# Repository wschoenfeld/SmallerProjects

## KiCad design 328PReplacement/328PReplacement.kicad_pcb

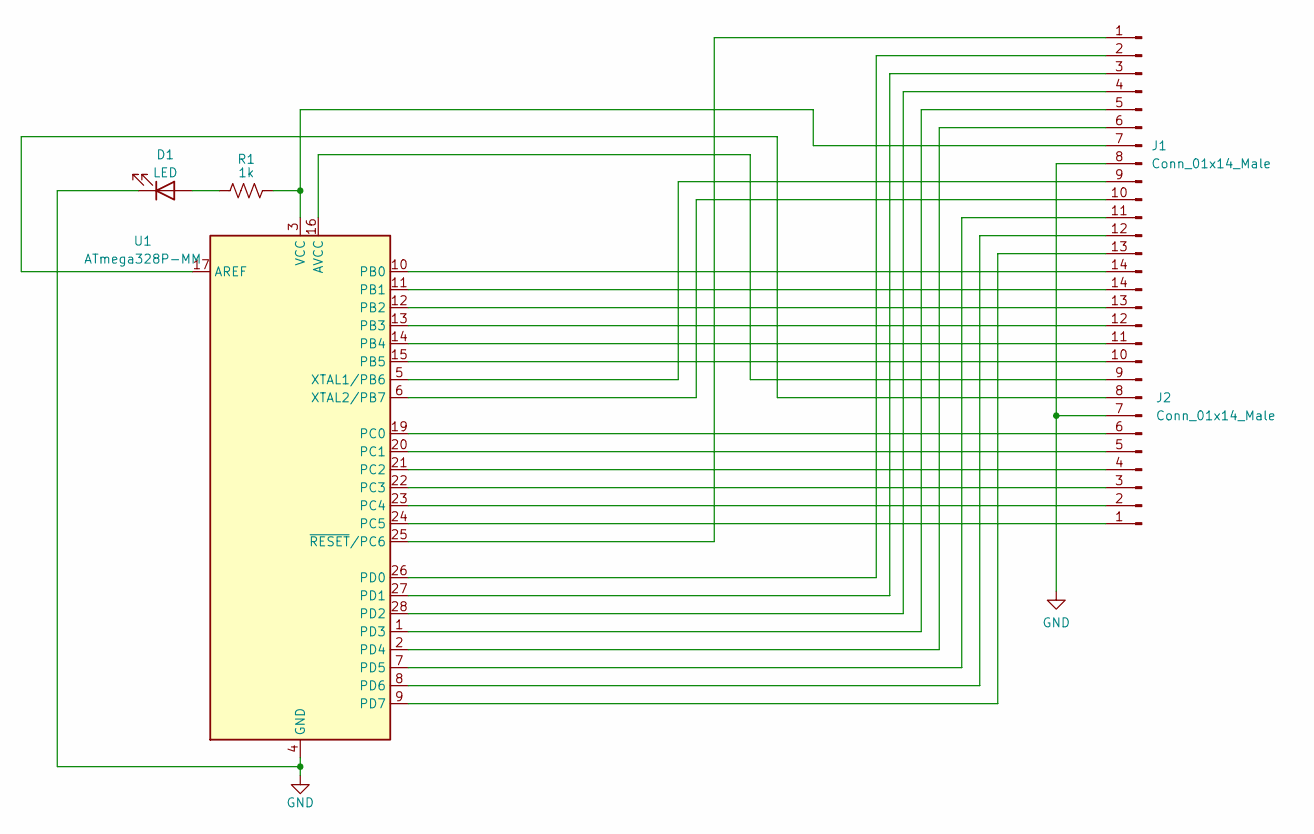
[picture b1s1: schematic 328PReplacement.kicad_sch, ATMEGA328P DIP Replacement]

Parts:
D1: LED; LED_0402_1005Metric
J1, J2: Conn_01x14_Male; PinHeader_1x14_P2.54mm_Vertical
R1: 1k; R_0402_1005Metric
U1: ATmega328P-MM; QFN-28-1EP_4x4mm_P0.45mm_EP2.4x2.4mm

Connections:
GND: D1.1 (K), J1.8, J2.7, U1.4 (GND), U1.18 (GND), U1.29 (GND)
unnamed: D1.2 (A), R1.1
unnamed: J1.1, U1.25 (~RESET/PC6)
unnamed: J1.2, U1.26 (PD0)
unnamed: J1.3, U1.27 (PD1)
unnamed: J1.4, U1.28 (PD2)
unnamed: J1.5, U1.1 (PD3)
unnamed: J1.6, U1.2 (PD4)
unnamed: J1.7, R1.2, U1.3 (VCC)
unnamed: J1.9, U1.5 (XTAL1/PB6)
unnamed: J1.10, U1.6 (XTAL2/PB7)
unnamed: J1.11, U1.7 (PD5)
unnamed: J1.12, U1.8 (PD6)
unnamed: J1.13, U1.9 (PD7)
unnamed: J1.14, U1.10 (PB0)
unnamed: J2.1, U1.24 (PC5)
unnamed: J2.2, U1.23 (PC4)
unnamed: J2.3, U1.22 (PC3)
unnamed: J2.4, U1.21 (PC2)
unnamed: J2.5, U1.20 (PC1)
unnamed: J2.6, U1.19 (PC0)
unnamed: J2.8, U1.17 (AREF)
unnamed: J2.9, U1.16 (AVCC)
unnamed: J2.10, U1.15 (PB5)
unnamed: J2.11, U1.14 (PB4)
unnamed: J2.12, U1.13 (PB3)
unnamed: J2.13, U1.12 (PB2)
unnamed: J2.14, U1.11 (PB1)

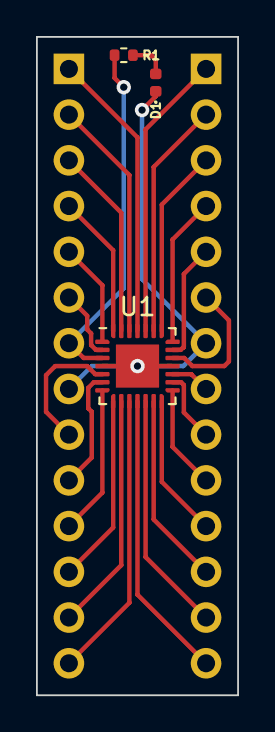
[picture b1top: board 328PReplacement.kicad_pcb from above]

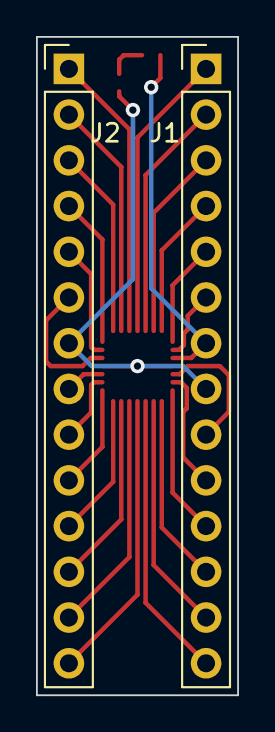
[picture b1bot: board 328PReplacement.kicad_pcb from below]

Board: 2 copper layers, 11.2 x 36.6 mm, 5 parts (2 on the bottom side), 28 nets.

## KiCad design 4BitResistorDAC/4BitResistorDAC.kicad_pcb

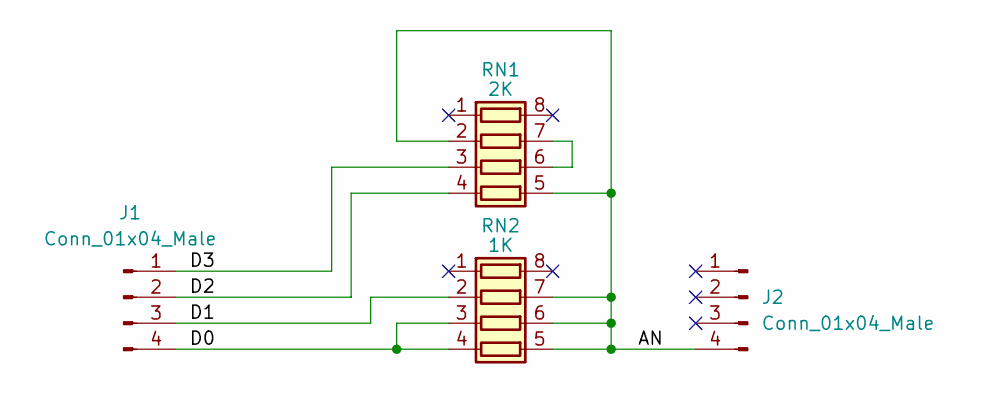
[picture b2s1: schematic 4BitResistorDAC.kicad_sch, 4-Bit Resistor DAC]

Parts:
J1, J2: Conn_01x04_Male; PinHeader_1x04_P2.54mm_Vertical
RN1: 2K; R_Array_Convex_4x0603
RN2: 1K; R_Array_Convex_4x0603

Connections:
/AN: J2.4, RN1.2 (R2.1), RN1.5 (R4.2), RN2.5 (R4.2), RN2.6 (R3.2), RN2.7 (R2.2)
/D0: J1.4, RN2.3 (R3.1), RN2.4 (R4.1)
/D1: J1.3, RN2.2 (R2.1)
/D2: J1.2, RN1.4 (R4.1)
/D3: J1.1, RN1.3 (R3.1)
unnamed: RN1.6 (R3.2), RN1.7 (R2.2)

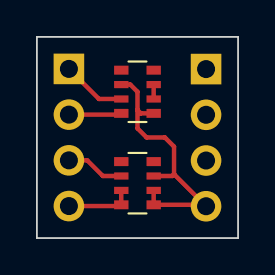
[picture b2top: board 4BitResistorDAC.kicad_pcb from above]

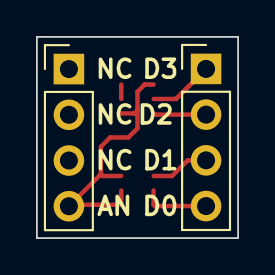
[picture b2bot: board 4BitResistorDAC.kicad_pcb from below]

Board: 2 copper layers, 11.2 x 11.2 mm, 4 parts (2 on the bottom side), 6 nets.

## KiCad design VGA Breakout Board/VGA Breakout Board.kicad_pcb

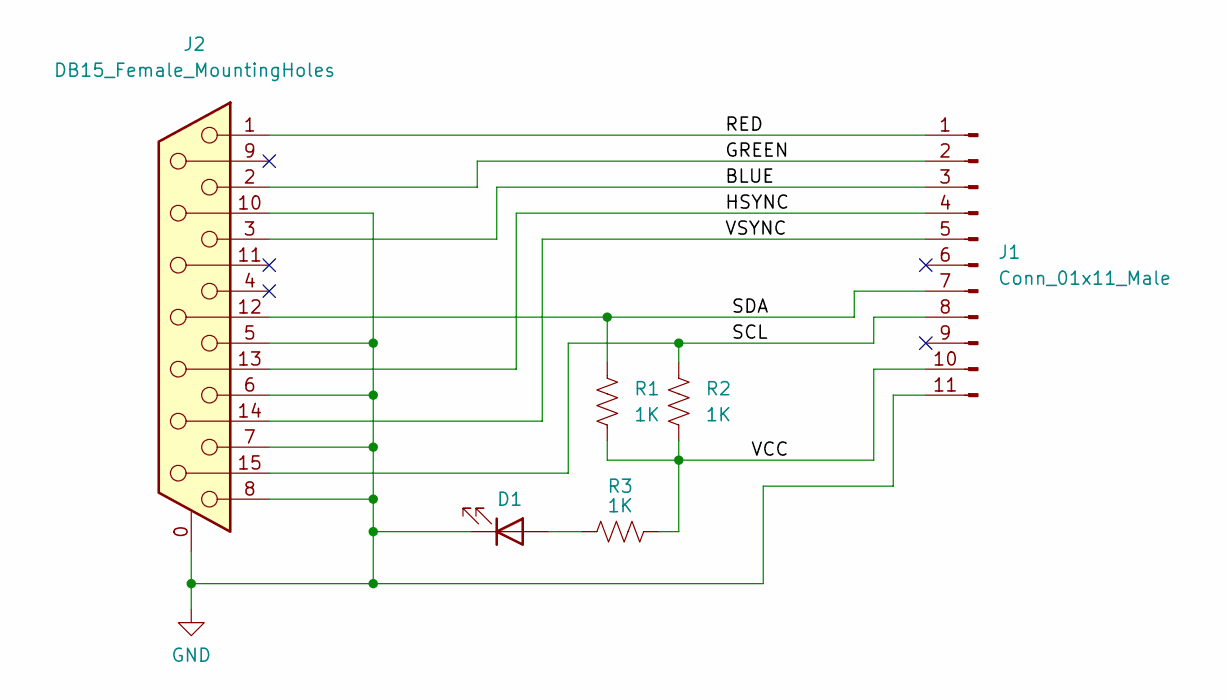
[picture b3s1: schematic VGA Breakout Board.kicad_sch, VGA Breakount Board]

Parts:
D1: LED; LED_0805_2012Metric_Pad1.15x1.40mm_HandSolder
J1: Conn_01x11_Male; PinHeader_1x11_P2.54mm_Vertical
J2: DB15_Female_MountingHoles; DSUB-15-HD_Female_Horizontal_P2.29x1.98mm_EdgePinOffset3.03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
R1, R2, R3: 1K; R_0805_2012Metric_Pad1.20x1.40mm_HandSolder

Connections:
/BLUE: J1.3, J2.3
/GREEN: J1.2, J2.2
/HSYNC: J1.4, J2.13
/RED: J1.1, J2.1
/SCL: J1.8, J2.15, R2.1
/SDA: J1.7, J2.12, R1.1
/VCC: J1.10, R1.2, R2.2, R3.2
/VSYNC: J1.5, J2.14
GND: D1.1 (K), J1.11, J2.0 (PAD), J2.5, J2.6, J2.7, J2.8, J2.10
unnamed: D1.2 (A), R3.1

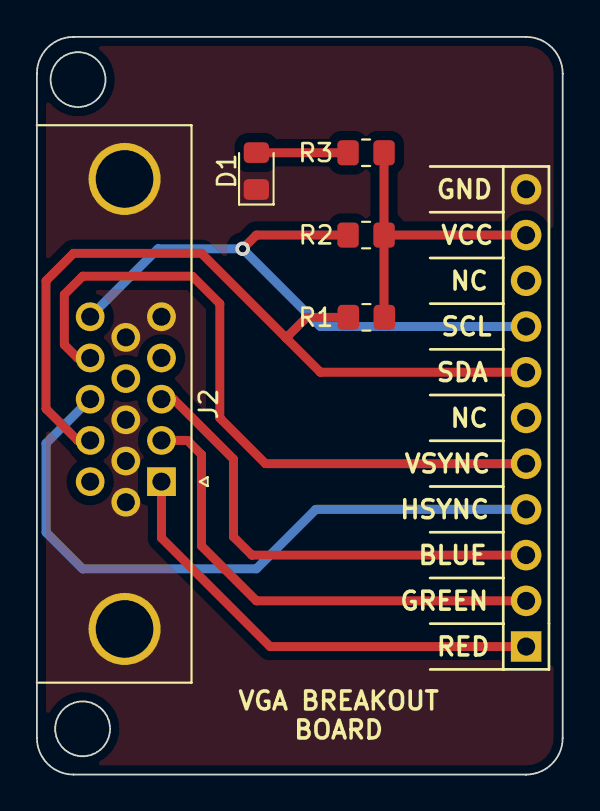
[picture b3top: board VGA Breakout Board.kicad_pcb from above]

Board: 2 copper layers, 29.2 x 41.0 mm, 6 parts (1 on the bottom side), 10 nets.

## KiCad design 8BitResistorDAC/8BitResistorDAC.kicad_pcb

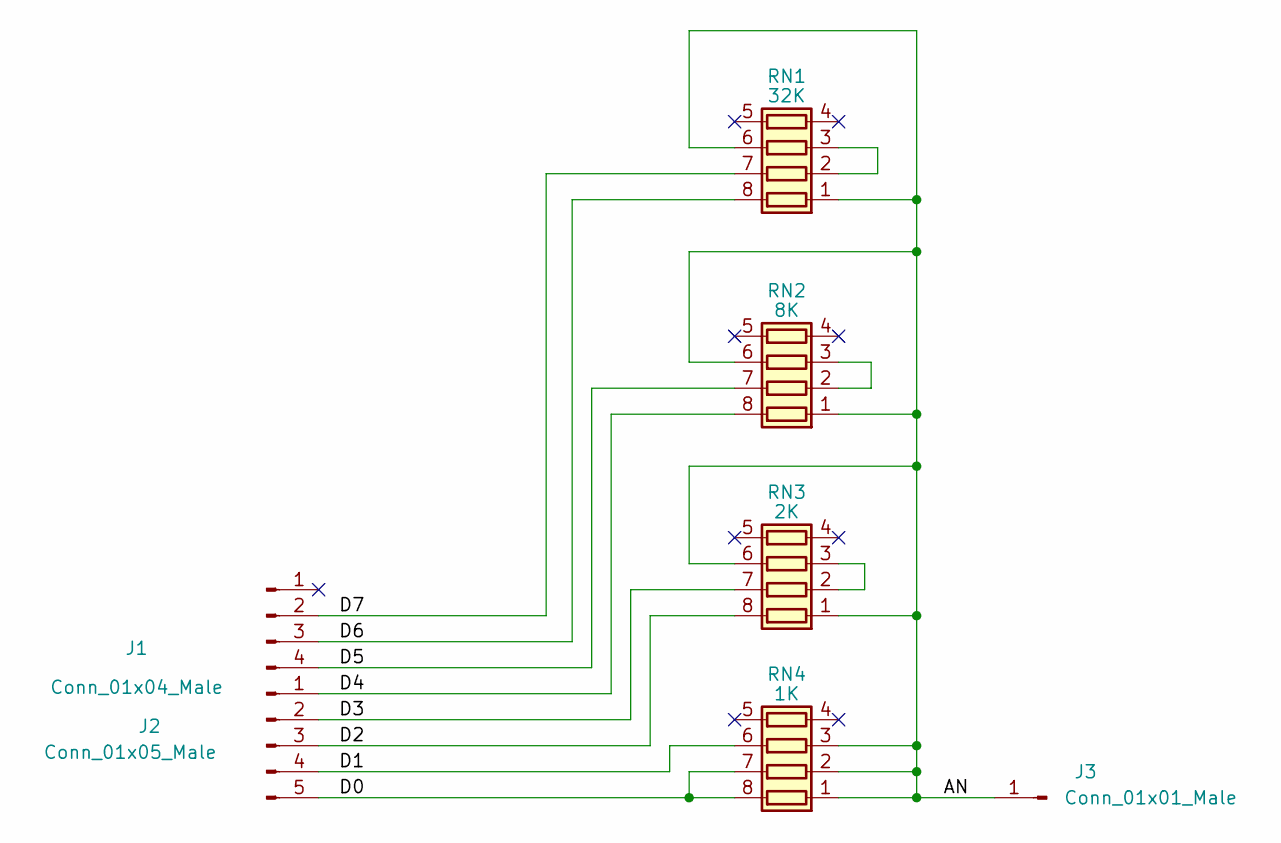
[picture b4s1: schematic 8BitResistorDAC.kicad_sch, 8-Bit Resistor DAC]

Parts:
J1: Conn_01x04_Male; PinHeader_1x04_P2.54mm_Vertical
J2: Conn_01x05_Male; PinHeader_1x05_P2.54mm_Vertical
J3: Conn_01x01_Male; PinHeader_1x01_P2.54mm_Vertical
RN1: 32K; R_Array_Convex_4x0603
RN2: 8K; R_Array_Convex_4x0603
RN3: 2K; R_Array_Convex_4x0603
RN4: 1K; R_Array_Convex_4x0603

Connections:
/AN: J3.1, RN1.1 (R1.1), RN1.6 (R3.2), RN2.1 (R1.1), RN2.6 (R3.2), RN3.1 (R1.1), RN3.6 (R3.2), RN4.1 (R1.1), RN4.2 (R2.1), RN4.3 (R3.1)
/D0: J2.5, RN4.7 (R2.2), RN4.8 (R1.2)
/D1: J2.4, RN4.6 (R3.2)
/D2: J2.3, RN3.8 (R1.2)
/D3: J2.2, RN3.7 (R2.2)
/D4: J2.1, RN2.8 (R1.2)
/D5: J1.4, RN2.7 (R2.2)
/D6: J1.3, RN1.8 (R1.2)
/D7: J1.2, RN1.7 (R2.2)
unnamed: RN1.2 (R2.1), RN1.3 (R3.1)
unnamed: RN2.2 (R2.1), RN2.3 (R3.1)
unnamed: RN3.2 (R2.1), RN3.3 (R3.1)

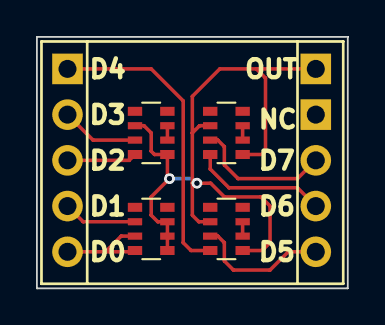
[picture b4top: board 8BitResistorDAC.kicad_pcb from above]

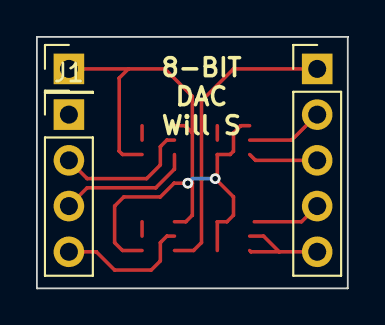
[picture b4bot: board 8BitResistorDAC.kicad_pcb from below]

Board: 2 copper layers, 17.3 x 14.0 mm, 7 parts (3 on the bottom side), 12 nets.

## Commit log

2022-12-12 Uploaded 2 Projects
2022-12-14 An SMT replacement board for a DIP-28 ATMEGA328P
